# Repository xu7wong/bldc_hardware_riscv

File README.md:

# bldc_hardware_riscv

Ki-Cad 6.99 project
Windows version download:

https://mirrors.tuna.tsinghua.edu.cn/kicad/windows/nightly/

Teardrop config file:

https://forum.kicad.info/t/kicad6-99-finally-added-the-teardrop-feature-non-plugins/33192

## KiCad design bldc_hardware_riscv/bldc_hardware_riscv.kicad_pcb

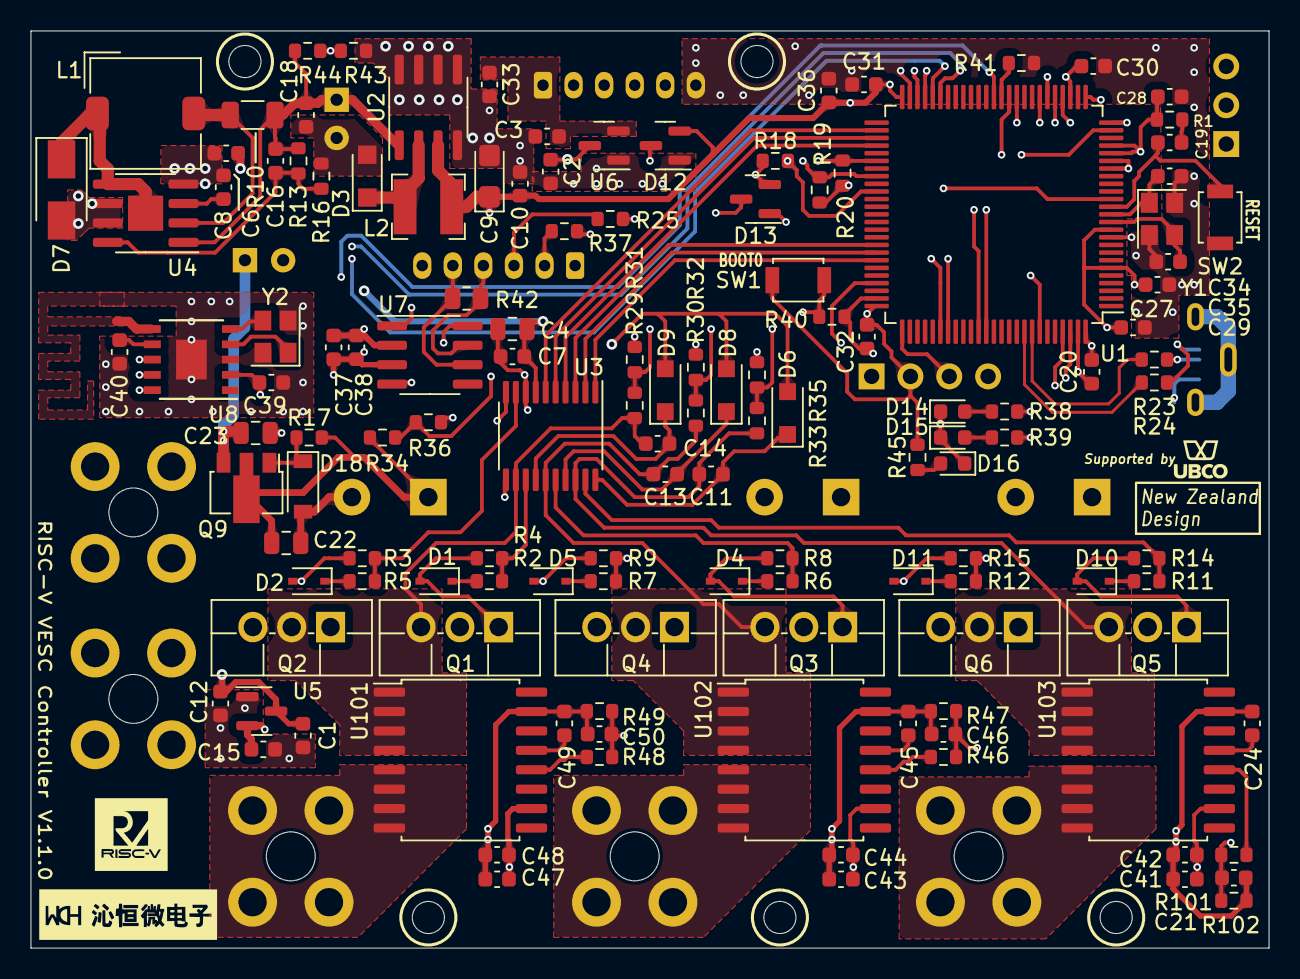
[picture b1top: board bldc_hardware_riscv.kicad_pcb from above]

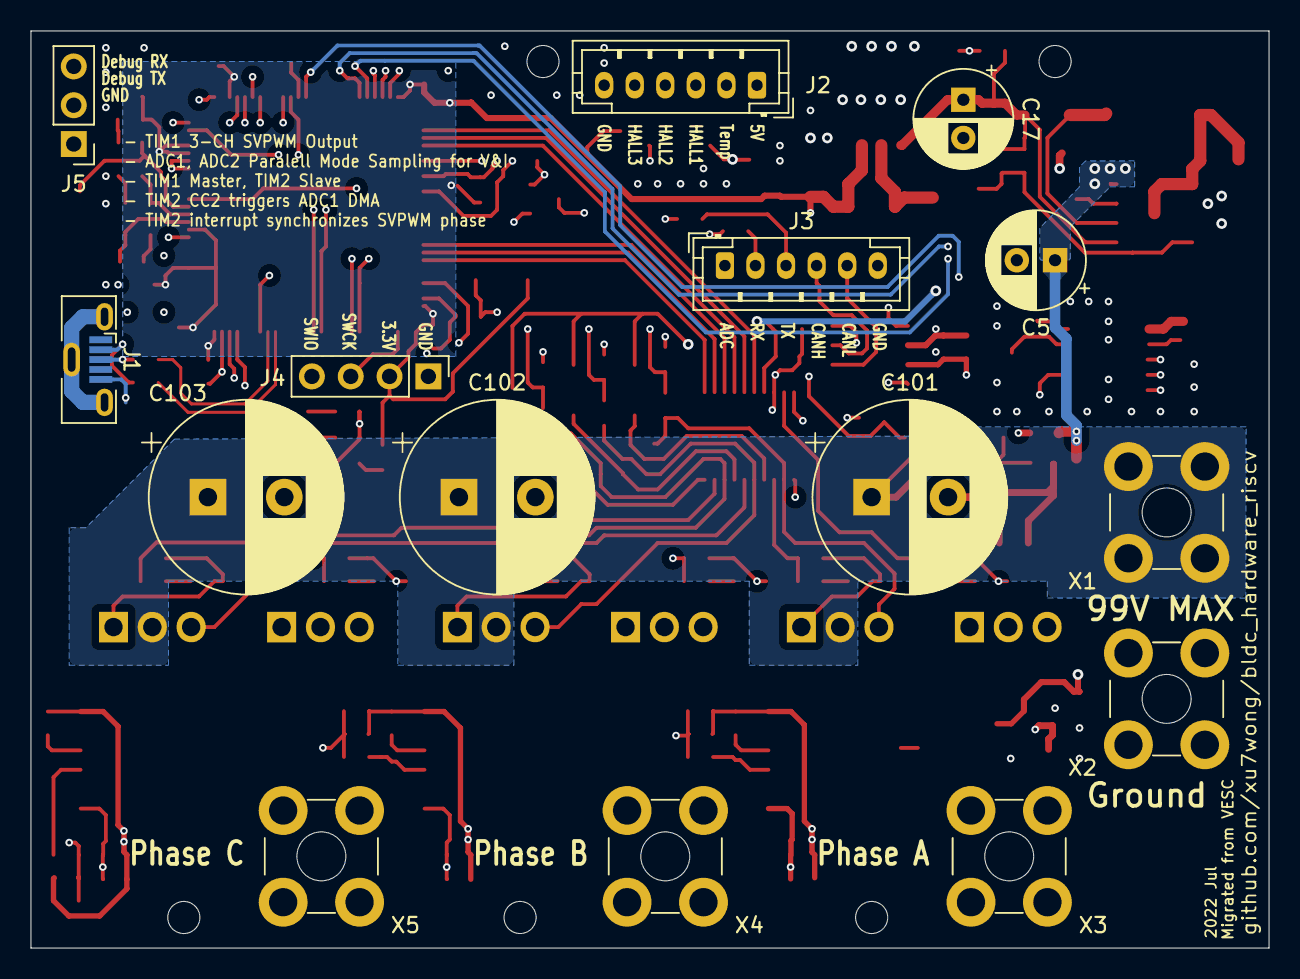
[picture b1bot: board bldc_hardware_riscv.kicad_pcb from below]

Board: 4 copper layers, 81.0 x 60.0 mm, 148 parts (15 on the bottom side), 98 nets.

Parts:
C1, C33, C36, C37, C39, C41, C43, C47: 2.2uF; C_0603_1608Metric
C2, C3, C6, C7, C10, C12, C15, C18, C19, C20, C27, C28, C29, C30, C31, C32, C38, C40, C42, C44, C48: 0.1uF; C_0603_1608Metric
C4: 2.2uF; C_0805_2012Metric
C5: 22uF/80V; CP_Radial_D6.3mm_P2.50mm
C8: 1uF; C_0603_1608Metric
C9: 100uF/6.3V; CP_EIA-3216-18_Kemet-A
C11, C13, C14: 0.22uF; C_0603_1608Metric
C16, C21, C24, C45, C46, C49, C50: 100pF; C_0603_1608Metric
C17: 330uF/16V; CP_Radial_D6.3mm_P2.50mm
C22, C23: 0.1uF; C_0805_2012Metric
C34, C35: 9pF; C_0603_1608Metric
C101, C102, C103: 220uF/80V; CP_Radial_D12.5mm_P5.00mm
D1, D2, D4, D5, D10, D11: 1N4148WS; D_SOD-323
D3: DSS34; Nexperia_CFP3_SOD-123W
D6, D8, D9: ES1002FL Panjit; D_SOD-123F
D7: ES1B; D_SMA
D12, D13: BAS40-04; SOT-23
D14, D15, D16: LED; LED_0603_1608Metric
D18: 75V; D_SOD-123
J1: USB_B_Micro Vertical; USB_Micro-B_Molex-105133-0001
J2, J3: 2.00mm JST 6Pin; JST_PH_B6B-PH-K_1x06_P2.00mm_Vertical
J4: Screw_Terminal_01x04; PinHeader_1x04_P2.54mm_Vertical
J5: Screw_Terminal_01x03; PinHeader_1x03_P2.54mm_Vertical
L1: 100uH/1.5A; L_TDK_SLF7032
L2: 33uH/1A; L_Bourns-SRN4018
Q1, Q2, Q3, Q4, Q5, Q6: 80V/200A; TO-220F-3_Vertical
Q9: FCX495; SOT-89-3
R1: 10K; R_0603_1608Metric
R2, R3, R4, R5, R6, R7, R8, R9, R11, R12, R14, R15, R23, R24, R25, R37: 4.7; R_0603_1608Metric
R10: 0.082; R_1206_3216Metric
R13: 19.1K; R_0603_1608Metric
R16, R18, R19, R20, R31, R32, R35, R36, R38, R39, R40, R41, R43, R46, R48, R101: 2K2; R_0603_1608Metric
R17: 150K; R_0603_1608Metric
R29, R30, R33, R34: 56K; R_0603_1608Metric
R42: 120; R_0805_2012Metric
R44: 27K; R_0603_1608Metric
R45, R47, R49, R102: 4K3; R_0603_1608Metric
SW1, SW2: B3U-1000P; SW_SPST_B3U-1000P
U1: CH32V307VCT6; LQFP-100_14x14mm_P0.5mm
U2: XL1509-3.3 XLSEMI; SOIC-8_3.9x4.9mm_P1.27mm
U3: EG2134 EG Micro; TSSOP-20_4.4x6.5mm_P0.65mm
U4: XL7046 XLSEMI; HSOP-8-1EP_3.9x4.9mm_P1.27mm_EP2.3x2.3mm
U5, U6: RT9058-50GVL Richtek; SOT-23
U7: SN65HVD230; SOIC-8_3.9x4.9mm_P1.27mm
U8: CH9141K; SSOP-10_3.9x4.9mm_P1.00mm
U101, U102, U103: MT9222WT-65BR5; SOIC-16W_7.5x10.3mm_P1.27mm
X1, X2, X3, X4, X5: Keystone-7693
Y1: 8MHz 3225; Oscillator_SMD_Abracon_ASE-4Pin_3.2x2.5mm
Y2: 32MHz 3225; Oscillator_SMD_Abracon_ASE-4Pin_3.2x2.5mm

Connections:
/3.3V: C9.1, C10.1, C20.1, C27.1, C28.1, C29.1, C30.1, C31.1, C32.1, C36.1, C37.1, C38.1, C39.1, D12.2, D13.2, J4.2, L2.2, R1.2, R18.2, R19.2, R20.2, R45.2, SW1.2, U1.6 (VBAT), U1.11 (VDD), U1.21 (VREF+), U1.22 (VDDA), U1.28 (VDD), U1.50 (VDD), U1.75 (VDD), U1.100 (VDD), U2.3 (FB), U7.3 (VCC), U8.2 (VCC)
/ADC_EXT: D13.3, J3.1, U1.36 (PB1/ADC9)
/AIN_CS1: C50.1, R48.2, R49.1, U1.30 (PA5/ADC5/DAC1)
/AIN_CS2: C46.1, R46.2, R47.1, U1.31 (PA6/ADC6)
/AIN_CS3: C21.1, R101.2, R102.1, U1.32 (PA7/ADC7)
/AIN_V12V: R43.1, R44.2, U1.24 (PA1/ADC1)
/AIN_VIN: R34.2, R36.1, U1.35 (PB0/ADC8)
/AIN_VS1: R29.2, R31.1, U1.25 (PA2/ADC2)
/AIN_VS2: R30.2, R32.1, U1.26 (PA3/ADC3)
/AIN_VS3: R33.2, R35.1, U1.29 (PA4/ADC4/DAC0)
/BLE_MODE: U1.38 (PE7), U8.10 (AT)
/BLE_RX: U1.46 (PE15), U8.9 (TXD)
/BLE_TX: U1.45 (PE14), U8.8 (RXD)
/BOOT0: R40.1, SW1.1, U1.94 (BOOT0)
/BOOT1: R41.1, U1.37 (PB2/BOOT1)
/CAN-R: U1.81 (PD0), U7.4 (R)
/CAN-T: U1.82 (PD1), U7.1 (D)
/CANH: J3.4, R42.2, U7.7 (CANH)
/CANL: J3.5, R42.1, U7.6 (CANL)
/D+: R23.2, U1.93 (PB7/USB2DP)
/D-: R24.2, U1.92 (PB6/USB2DM)
/DEBUG_RX: J5.3, U1.48 (PB11)
/DEBUG_TX: J5.2, U1.47 (PB10)
/Driver/5V: C15.1, C41.2, C42.2, C43.2, C44.2, C47.2, C48.2, U5.2 (VO), U101.10 (VCC), U102.10 (VCC), U103.10 (VCC)
/Driver/12V: C1.1, C2.1, C4.1, C7.1, C12.1, C16.1, C17.1, C18.1, D6.2 (A), D8.2 (A), D9.2 (A), R10.2, R13.1, R44.1, U2.1 (VIN), U3.7 (VCC), U4.1 (CSN), U5.3 (VI), U6.3 (VI)
/Driver/75V: C5.1, C6.1, C8.1, C23.2, Q9.3 (E), U4.4 (VIN)
/Driver/99V: C22.1, C101.1, C102.1, C103.1, Q1.2 (D), Q3.2 (D), Q5.2 (D), Q9.2 (C), R17.2, R34.1, X1.1
/Driver/HO1: R2.1, R4.1, U3.13 (HO3)
/Driver/HO2: R6.1, R8.1, U3.16 (HO2)
/Driver/HO3: R11.1, R14.1, U3.19 (HO1)
/Driver/LO1: R3.1, R5.1, U3.9 (LO3)
/Driver/LO2: R7.1, R9.1, U3.10 (LO2)
/Driver/LO3: R12.1, R15.1, U3.11 (LO1)
/Driver/PhaseA: U101.5 (IP-), U101.6 (IP-), U101.7 (IP-), U101.8 (IP-), X3.1
/Driver/PhaseB: U102.5 (IP-), U102.6 (IP-), U102.7 (IP-), U102.8 (IP-), X4.1
/Driver/PhaseC: U103.5 (IP-), U103.6 (IP-), U103.7 (IP-), U103.8 (IP-), X5.1
/Driver/VS1: C14.2, Q1.3 (S), Q2.2 (D), R29.1, U3.12 (VS3), U101.1 (IP+), U101.2 (IP+), U101.3 (IP+), U101.4 (IP+)
/Driver/VS2: C13.2, Q3.3 (S), Q4.2 (D), R30.1, U3.15 (VS2), U102.1 (IP+), U102.2 (IP+), U102.3 (IP+), U102.4 (IP+)
/Driver/VS3: C11.2, Q5.3 (S), Q6.2 (D), R33.1, U3.18 (VS1), U103.1 (IP+), U103.2 (IP+), U103.3 (IP+), U103.4 (IP+)
/HALL1: J2.3, R20.1, U1.56 (PD9)
/HALL2: J2.4, R19.1, U1.58 (PD11)
/HALL3: J2.5, R18.1, U1.60 (PD13)
/HALL-VCC: C3.1, C33.1, J2.1, U6.2 (VO)
/LED1: R38.2, U1.97 (PE0)
/LED2: R39.2, U1.98 (PE1)
/MOTOR-TEMP: D12.3, J2.2, U1.15 (PC0/ADC10)
/NRST: C19.2, SW2.1, U1.14 (NRST)
/SWCK: J4.3, U1.76 (PA14/SWCLK)
/SWIO: J4.4, U1.72 (PA13/SWDIO)
/TIM1-CH1: U1.67 (PA8), U3.3 (HN3)
/TIM1-CH1N: U1.52 (PB13), U3.6 (LN3)
/TIM1-CH2: U1.68 (PA9), U3.2 (HN2)
/TIM1-CH2N: U1.53 (PB14), U3.5 (LN2)
/TIM1-CH3: U1.69 (PA10), U3.1 (HN1)
/TIM1-CH3N: U1.54 (PB15), U3.4 (LN1)
/UART_R: R37.1, U1.87 (PD6)
/UART_T: R25.1, U1.86 (PD5)
/XI: C35.1, U1.12 (OSC_IN), Y1.3
/XO: C34.1, U1.13 (OSC_OUT), Y1.1
GND: C1.2, C2.2, C3.2, C4.2, C5.2, C6.2, C7.2, C9.2, C10.2, C12.2, C15.2, C17.2, C18.2, C20.2, C21.2, C22.2, C23.1, C24.2, C27.2, C28.2, C29.2, C30.2, C31.2, C32.2, C33.2, C34.2, C35.2, C36.2, C37.2, C38.2, C39.2, C40.2, C41.1, C42.1, C43.1, C44.1, C45.2, C46.2, C47.1, C48.1, C49.2, C50.2, C101.2, C102.2, C103.2, D3.2 (A), D7.2 (A), D12.1, D13.1, D14.1 (K), D15.1 (K), D16.1 (K), D18.2 (A), J1.5 (GND), J2.6, J3.6, J4.1, J5.1, Q2.3 (S), Q4.3 (S), Q6.3 (S), R16.2, R31.2, R32.2, R35.2, R36.2, R40.2, R41.2, R43.2, R47.2, R49.2, R102.2, SW2.2, U1.10 (VSS), U1.19 (VSSA), U1.20 (VREF-), U1.27 (VSS), U1.49 (VSS), U1.74 (VSS), U1.99 (VSS), U2.4 (ON), U2.5 (GND), U2.6 (GND), U2.7 (GND), U2.8 (GND), U3.8 (GND), U4.6 (EN), U4.7 (GND), U5.1 (GND), U6.1 (GND), U7.2 (GND), U7.8 (Rs), U8.3 (GND), U8.6 (ANT), U8.11 (GND), U101.15 (GND), U102.15 (GND), U103.15 (GND), X2.1, Y1.2, Y1.4, Y2.2, Y2.4
unnamed: C19.1, R1.1
unnamed: D1.2 (A), Q1.1 (G), R4.2
unnamed: D1.1 (K), R2.2
unnamed: D2.2 (A), Q2.1 (G), R5.2
unnamed: D2.1 (K), R3.2
unnamed: D3.1 (K), L2.1, U2.2 (OUT)
unnamed: D4.2 (A), Q3.1 (G), R8.2
unnamed: D4.1 (K), R6.2
unnamed: D5.2 (A), Q4.1 (G), R9.2
unnamed: D5.1 (K), R7.2
unnamed: C11.1, D6.1 (K), U3.20 (VB1)
unnamed: D7.1 (K), L1.1, U4.5 (SW), U4.9 (SW)
unnamed: C13.1, D8.1 (K), U3.17 (VB2)
unnamed: C14.1, D9.1 (K), U3.14 (VB3)
unnamed: D10.2 (A), Q5.1 (G), R14.2
unnamed: D10.1 (K), R11.2
unnamed: D11.2 (A), Q6.1 (G), R15.2
unnamed: D11.1 (K), R12.2
unnamed: D14.2 (A), R38.1
unnamed: D15.2 (A), R39.1
unnamed: D16.2 (A), R45.1
unnamed: D18.1 (K), Q9.1 (B), R17.1
unnamed: J1.3 (D+), R23.1
unnamed: J1.2 (D-), R24.1
unnamed: J3.2, R37.2
unnamed: J3.3, R25.2
unnamed: L1.2, R10.1, U4.2 (CSP)
unnamed: C16.2, R13.2, R16.1, U4.8 (FB)
unnamed: C8.2, U4.3 (VC)
unnamed: C40.1, U8.7 (VA)
unnamed: U8.4 (XI), Y2.1
unnamed: U8.5 (XO), Y2.3
unnamed: C49.1, U101.13 (FLT)
unnamed: R48.1, U101.12 (OUT)
unnamed: C45.1, U102.13 (FLT)
unnamed: R46.1, U102.12 (OUT)
unnamed: C24.1, U103.13 (FLT)
unnamed: R101.1, U103.12 (OUT)

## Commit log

2022-07-10 add sch & pcb
2022-07-11 First release to PCB manufacture
2022-07-11 add 2 pages schematic
2022-07-13 fix resistor/inductor/capacitor parameters, add boot button, add 120Ohm CAN bus load resistor.
2022-07-19 update gbr with teardrop
2022-07-19 add teardrop by Kicad V6.99
2022-07-19 add html BOM
2022-07-24 add debug RX/TX, fix CH9141K footprint error, add 12V detection
2022-07-25 fix PCB DRC error, fix CH9141K 3D preview
2022-07-25 update side A image
2022-08-06 use hall current sensor (60A limit), use keystone terminal, support up to 120V input
2022-08-06 add missed caps
2022-08-09 Update WCH LOGO, fixed gbr clearance issue (around MCU range)
